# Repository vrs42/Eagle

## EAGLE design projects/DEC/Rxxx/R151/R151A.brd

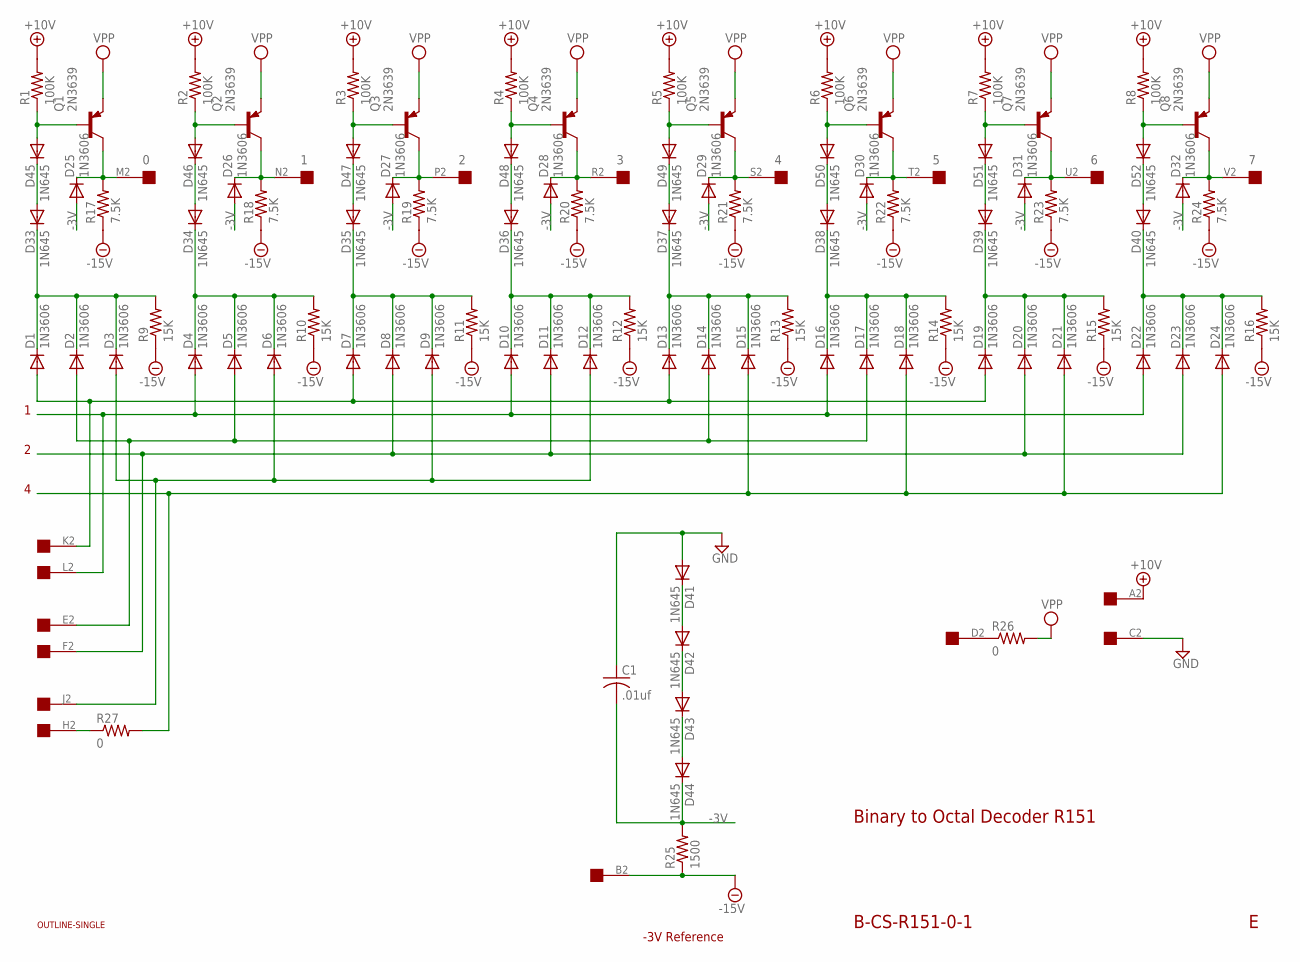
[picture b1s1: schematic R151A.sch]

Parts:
C1: .01uf; C050-025X075
D1, D2, D3, D4, D5, D6, D7, D8, D9, D10, D11, D12, D13, D14, D15, D16, D17, D18, D19, D20, D21, D22, D23, D24, D25, D26, D27, D28, D29, D30, D31, D32: 1N3606; DO35-10
D33, D34, D35, D36, D37, D38, D39, D40, D41, D42, D43, D44, D45, D46, D47, D48, D49, D50, D51, D52: 1N645; DO35-10
Q1, Q2, Q3, Q4, Q5, Q6, Q7, Q8: 2N3639; TO39
R1, R2, R3, R4, R5, R6, R7, R8: 100K; 0207/10
R9, R10, R11, R12, R13, R14, R15, R16: 15K; 0207/10
R17, R18, R19, R20, R21, R22, R23, R24: 7.5K; 0207/10
R25: 1500; 0207/10
R26, R27: 0; 0207/10
U$1: OUTLINE-SINGLE; SINGLE
U$2: EDGE-1; EDGE-CON1

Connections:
0: D25.C, Q1.3 (C), R17.2, U$2.M2
1: D26.C, Q2.3 (C), R18.2, U$2.N2
2: D27.C, Q3.3 (C), R19.2, U$2.P2
3: D28.C, Q4.3 (C), R20.2, U$2.R2
4: D29.C, Q5.3 (C), R21.2, U$2.S2
5: D30.C, Q6.3 (C), R22.2, U$2.T2
6: D31.C, Q7.3 (C), R23.2, U$2.U2
7: D32.C, Q8.3 (C), R24.2, U$2.V2
!D0: D1.A, D7.A, D13.A, D19.A, U$2.K2
!D1: D2.A, D5.A, D14.A, D17.A, U$2.E2
!D2: D3.A, D6.A, D9.A, D12.A, U$2.J2
+10V: R1.2, R2.2, R3.2, R4.2, R5.2, R6.2, R7.2, R8.2, U$2.A2
-3V: C1.2, D25.A, D26.A, D27.A, D28.A, D29.A, D30.A, D31.A, D32.A, D44.C, R25.2
-15V: R9.1, R10.1, R11.1, R12.1, R13.1, R14.1, R15.1, R16.1, R17.1, R18.1, R19.1, R20.1, R21.1, R22.1, R23.1, R24.1, R25.1, U$2.B2
D0: D4.A, D10.A, D16.A, D22.A, U$2.L2
D1: D8.A, D11.A, D20.A, D23.A, U$2.F2
D2: D15.A, D18.A, D21.A, D24.A, R27.2
GND: C1.1, D41.A, U$2.C2
unnamed: D46.A, Q2.2 (B), R2.1
unnamed: D41.C, D42.A
unnamed: R26.1, U$2.D2
unnamed: R27.1, U$2.H2
unnamed: D4.C, D5.C, D6.C, D34.C, R10.2
unnamed: D34.A, D46.C
unnamed: D47.A, Q3.2 (B), R3.1
unnamed: D7.C, D8.C, D9.C, D35.C, R11.2
unnamed: D35.A, D47.C
unnamed: D42.C, D43.A
unnamed: D43.C, D44.A
unnamed: D48.A, Q4.2 (B), R4.1
unnamed: D45.A, Q1.2 (B), R1.1
unnamed: D1.C, D2.C, D3.C, D33.C, R9.2
unnamed: D33.A, D45.C
unnamed: D10.C, D11.C, D12.C, D36.C, R12.2
unnamed: D36.A, D48.C
unnamed: D49.A, Q5.2 (B), R5.1
unnamed: D13.C, D14.C, D15.C, D37.C, R13.2
unnamed: D37.A, D49.C
unnamed: D50.A, Q6.2 (B), R6.1
unnamed: D16.C, D17.C, D18.C, D38.C, R14.2
unnamed: D38.A, D50.C
unnamed: D51.A, Q7.2 (B), R7.1
unnamed: D19.C, D20.C, D21.C, D39.C, R15.2
unnamed: D39.A, D51.C
unnamed: D52.A, Q8.2 (B), R8.1
unnamed: D22.C, D23.C, D24.C, D40.C, R16.2
unnamed: D40.A, D52.C
VPP: Q1.1 (E), Q2.1 (E), Q3.1 (E), Q4.1 (E), Q5.1 (E), Q6.1 (E), Q7.1 (E), Q8.1 (E), R26.2

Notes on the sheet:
Binary to Octal Decoder R151
B-CS-R151-0-1
-3V Reference

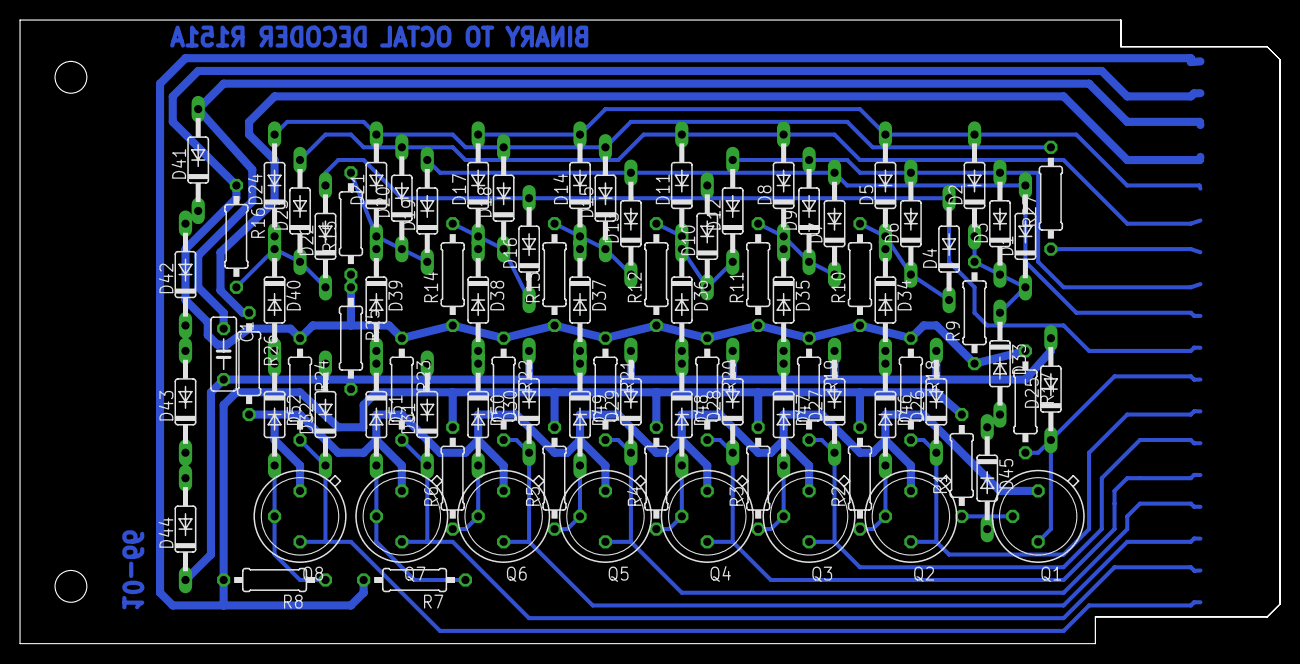
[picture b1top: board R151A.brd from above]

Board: 2 copper layers, 125.7 x 62.2 mm, 90 parts (0 on the bottom side), 48 nets.

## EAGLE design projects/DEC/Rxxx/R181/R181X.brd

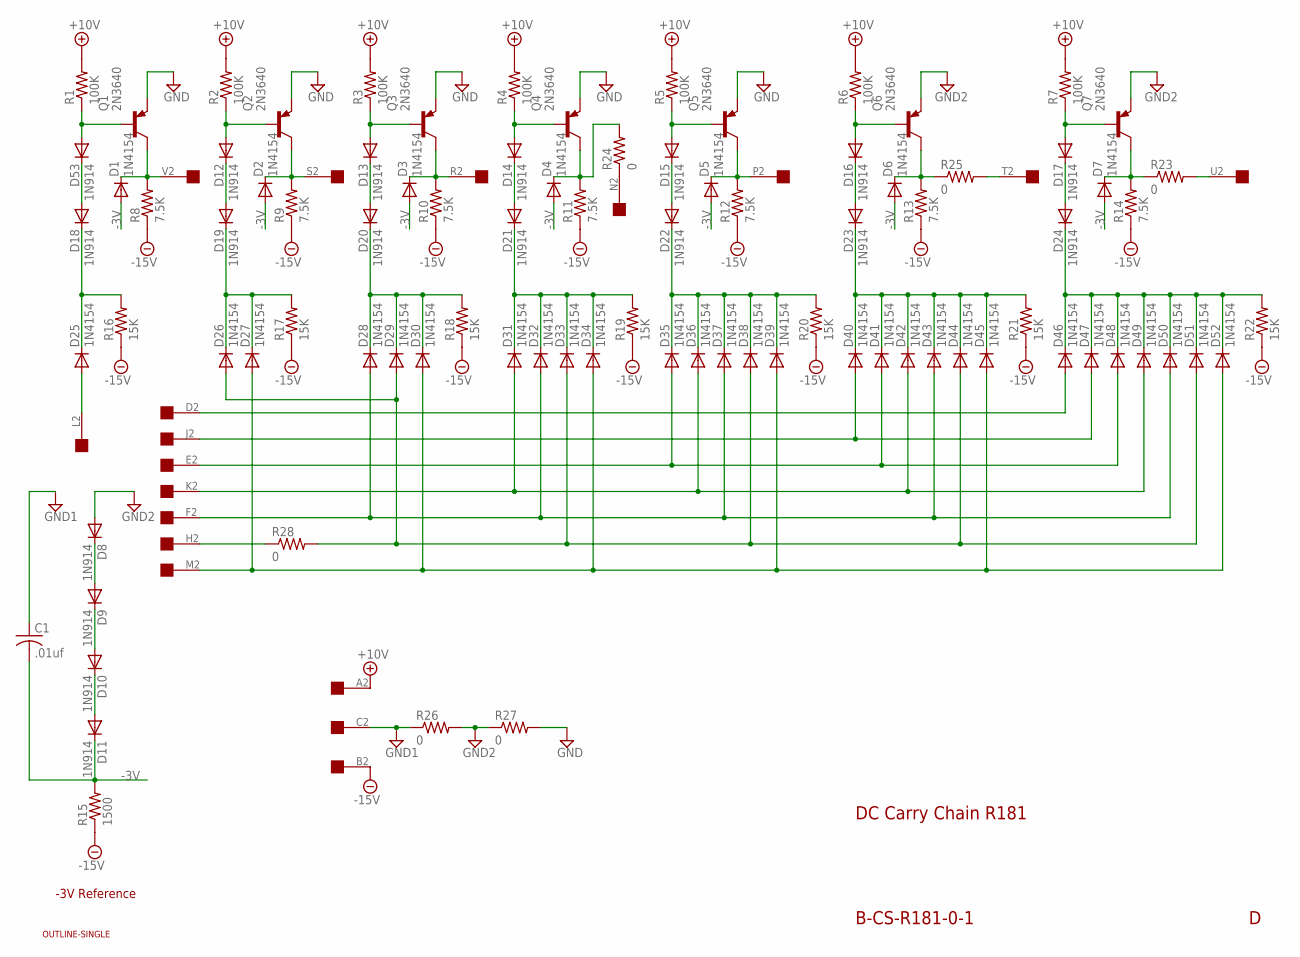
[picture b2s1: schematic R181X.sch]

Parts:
C1: .01uf; C050-025X075
D1, D2, D3, D4, D5, D6, D7, D25, D26, D27, D28, D29, D30, D31, D32, D33, D34, D35, D36, D37, D38, D39, D40, D41, D42, D43, D44, D45, D46, D47, D48, D49, D50, D51, D52: 1N4154; DO35-10
D8, D9, D10, D11, D12, D13, D14, D15, D16, D17, D18, D19, D20, D21, D22, D23, D24, D53: 1N914; DO35-10
Q1, Q2, Q3, Q4, Q5, Q6, Q7: 2N3640; TO39
R1, R2, R3, R4, R5, R6, R7: 100K; 0207/10
R8, R9, R10, R11, R12, R13, R14: 7.5K; 0207/10
R15: 1500; 0207/10
R16, R17, R18, R19, R20, R21, R22: 15K; 0207/10
R23, R24, R25, R26, R27, R28: 0; 0207/10
U$1: OUTLINE-SINGLE; SINGLE
U$2: EDGE-1; EDGE-CON1

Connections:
+10V: R1.2, R2.2, R3.2, R4.2, R5.2, R6.2, R7.2, U$2.A2
-3V: C1.2, D1.A, D2.A, D3.A, D4.A, D5.A, D6.A, D7.A, D11.C, R15.2
-15V: R8.1, R9.1, R10.1, R11.1, R12.1, R13.1, R14.1, R15.1, R16.1, R17.1, R18.1, R19.1, R20.1, R21.1, R22.1, U$2.B2
GND: Q1.1 (E), Q2.1 (E), Q3.1 (E), Q4.1 (E), Q5.1 (E), R27.2
GND1: C1.1, R26.1, U$2.C2
GND2: D8.A, Q6.1 (E), Q7.1 (E), R26.2, R27.1
N: D4.C, Q4.3 (C), R11.2, R24.2
unnamed: D26.A, D29.A, D33.A, D38.A, D44.A, D51.A, R28.2
unnamed: D12.A, Q2.2 (B), R2.1
unnamed: D8.C, D9.A
unnamed: R28.1, U$2.H2
unnamed: D25.A, U$2.L2
unnamed: D19.C, D26.C, D27.C, R17.2
unnamed: D12.C, D19.A
unnamed: D13.A, Q3.2 (B), R3.1
unnamed: D27.A, D30.A, D34.A, D39.A, D45.A, D52.A, U$2.M2
unnamed: D35.A, D41.A, D48.A, U$2.E2
unnamed: D20.C, D28.C, D29.C, D30.C, R18.2
unnamed: D13.C, D20.A
unnamed: D9.C, D10.A
unnamed: D28.A, D32.A, D37.A, D43.A, D50.A, U$2.F2
unnamed: D31.A, D36.A, D42.A, D49.A, U$2.K2
unnamed: D10.C, D11.A
unnamed: R23.2, U$2.U2
unnamed: D14.A, Q4.2 (B), R4.1
unnamed: D53.A, Q1.2 (B), R1.1
unnamed: D40.A, D47.A, U$2.J2
unnamed: R25.2, U$2.T2
unnamed: D18.C, D25.C, R16.2
unnamed: D18.A, D53.C
unnamed: D46.A, U$2.D2
unnamed: R24.1, U$2.N2
unnamed: D21.C, D31.C, D32.C, D33.C, D34.C, R19.2
unnamed: D14.C, D21.A
unnamed: D15.A, Q5.2 (B), R5.1
unnamed: D22.C, D35.C, D36.C, D37.C, D38.C, D39.C, R20.2
unnamed: D15.C, D22.A
unnamed: D16.A, Q6.2 (B), R6.1
unnamed: D23.C, D40.C, D41.C, D42.C, D43.C, D44.C, D45.C, R21.2
unnamed: D16.C, D23.A
unnamed: D17.A, Q7.2 (B), R7.1
unnamed: D24.C, D46.C, D47.C, D48.C, D49.C, D50.C, D51.C, D52.C, R22.2
unnamed: D17.C, D24.A
P: D5.C, Q5.3 (C), R12.2, U$2.P2
R: D3.C, Q3.3 (C), R10.2, U$2.R2
S: D2.C, Q2.3 (C), R9.2, U$2.S2
T: D6.C, Q6.3 (C), R13.2, R25.1
U: D7.C, Q7.3 (C), R14.2, R23.1
V: D1.C, Q1.3 (C), R8.2, U$2.V2

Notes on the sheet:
DC Carry Chain R181
B-CS-R181-0-1
-3V Reference

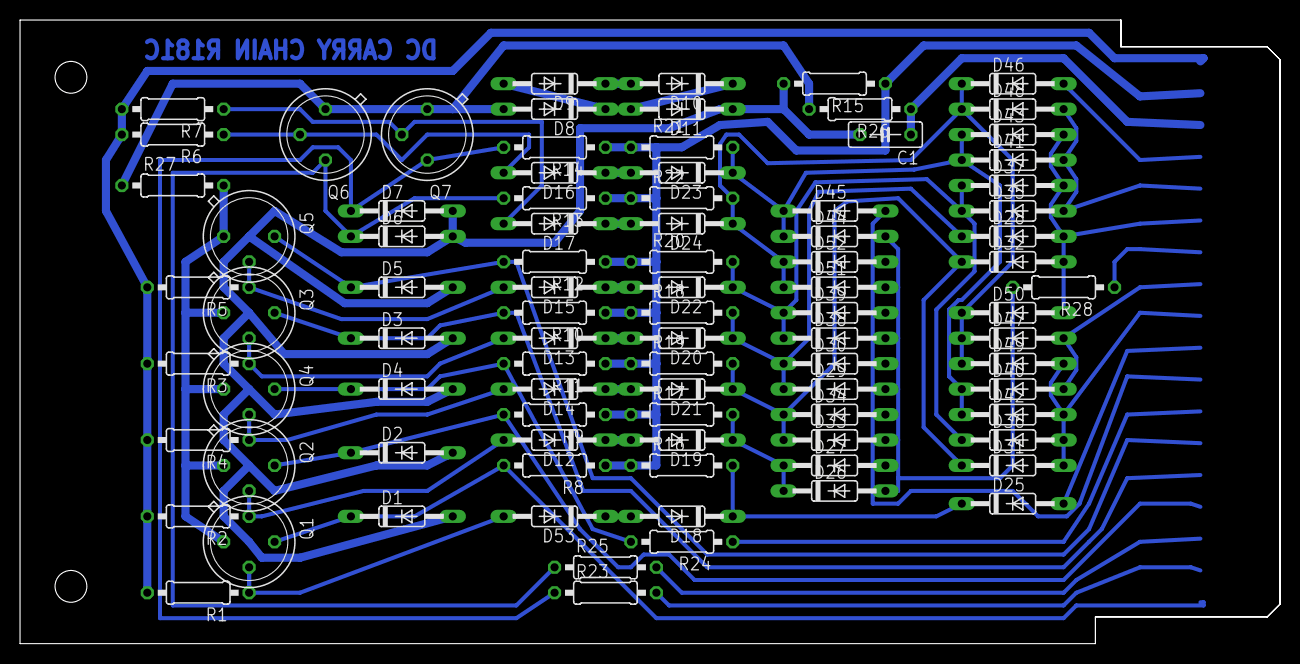
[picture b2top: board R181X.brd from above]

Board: 2 copper layers, 125.7 x 62.2 mm, 91 parts (0 on the bottom side), 49 nets.

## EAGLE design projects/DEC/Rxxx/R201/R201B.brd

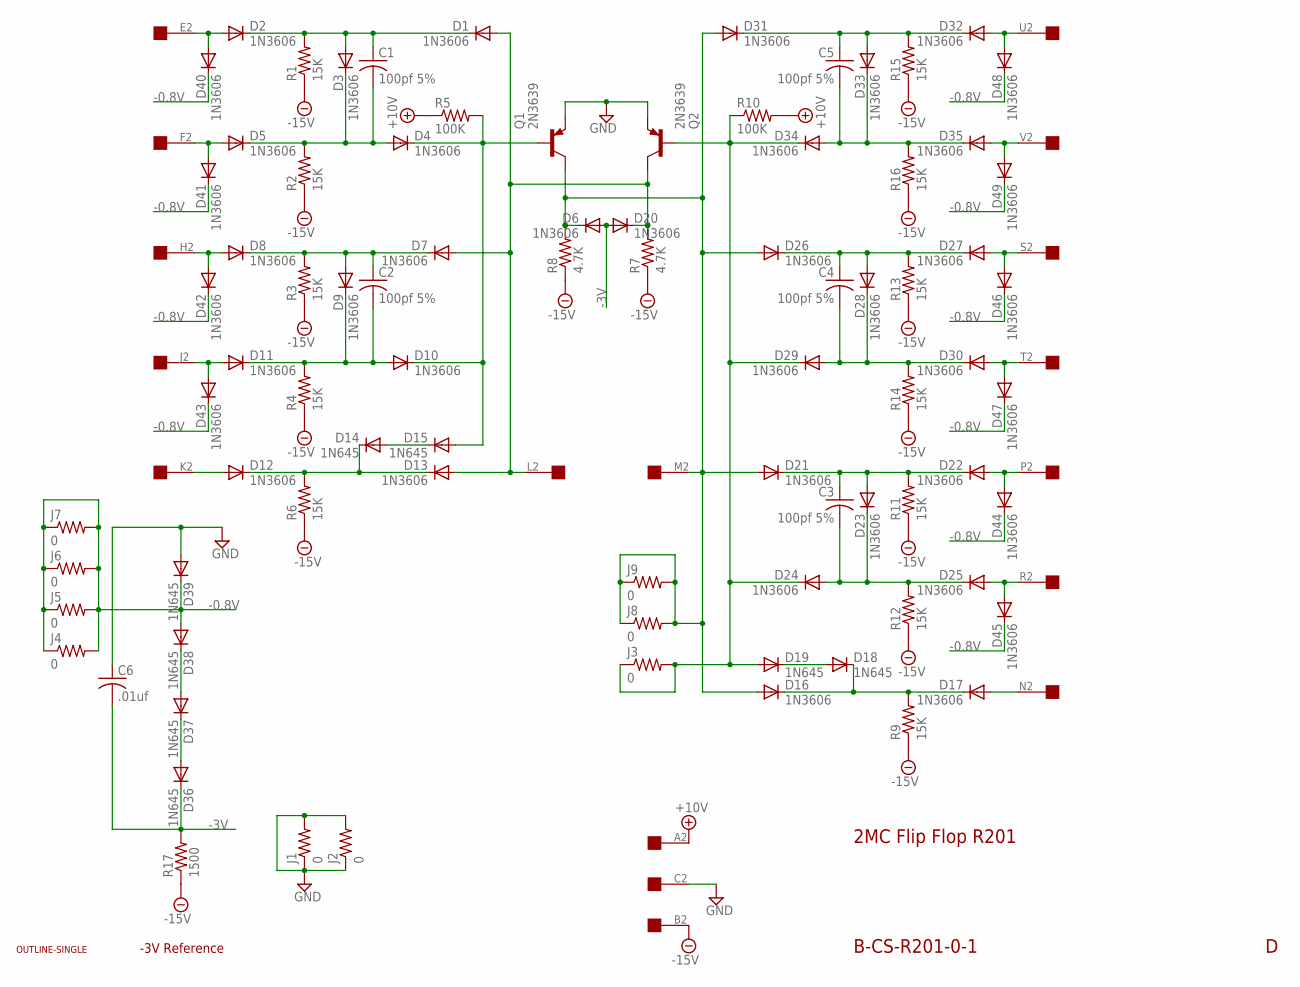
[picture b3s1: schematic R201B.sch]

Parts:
C1, C2, C3, C4, C5: 100pf 5%; C063-025X075
C6: .01uf; C063-025X075
D1, D2, D3, D4, D5, D6, D7, D8, D9, D10, D11, D12, D13, D16, D17, D20, D21, D22, D23, D24, D25, D26, D27, D28, D29, D30, D31, D32, D33, D34, D35, D40, D41, D42, D43, D44, D45, D46, D47, D48, D49: 1N3606; DO35-10
D14, D15, D18, D19, D36, D37, D38, D39: 1N645; DO35-10
J1, J2, J3, J4, J5, J6, J7, J8, J9: 0; 0207/10
Q1, Q2: 2N3639; TO39
R1, R2, R3, R4, R6, R9, R11, R12, R13, R14, R15, R16: 15K; 0207/10
R5, R10: 100K; 0207/10
R7, R8: 4.7K; 0207/10
R17: 1500; 0207/10
U$1: OUTLINE-SINGLE; SINGLE
U$2: EDGE-1; EDGE-CON1

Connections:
+10V: R5.1, R10.2, U$2.A2
-0.8V: D38.A, D39.C, D40.C, D41.C, D42.C, D43.C, D44.C, D45.C, D46.C, D47.C, D48.C, D49.C, J4.1, J4.2, J5.1, J5.2, J6.1, J6.2, J7.1, J7.2
-3V: C6.2, D6.A, D20.A, D36.C, R17.2
-15V: R1.1, R2.1, R3.1, R4.1, R6.1, R7.1, R8.1, R9.1, R11.1, R12.1, R13.1, R14.1, R15.1, R16.1, R17.1, U$2.B2
GND: C6.1, D39.A, J1.1, J1.2, J2.1, J2.2, Q1.1 (E), Q2.1 (E), U$2.C2
L: D1.A, D7.A, D13.A, D20.C, Q2.3 (C), R7.2, U$2.L2
M: D6.C, D16.A, D21.A, D26.A, D31.A, J8.1, J8.2, J9.1, J9.2, Q1.3 (C), R8.2, U$2.M2
unnamed: D5.A, D41.A, U$2.F2
unnamed: C5.1, D31.C, D32.C, D33.A, R15.2
unnamed: C1.2, D3.C, D4.A, D5.C, R2.2
unnamed: C1.1, D1.C, D2.C, D3.A, R1.2
unnamed: D12.A, U$2.K2
unnamed: D19.A, D24.C, D29.C, D34.C, J3.1, J3.2, Q2.2 (B), R10.1
unnamed: D32.A, D48.A, U$2.U2
unnamed: C5.2, D33.C, D34.A, D35.C, R16.2
unnamed: D17.A, U$2.N2
unnamed: D2.A, D40.A, U$2.E2
unnamed: D35.A, D49.A, U$2.V2
unnamed: D18.A, D19.C
unnamed: D37.A, D38.C
unnamed: D4.C, D10.C, D15.A, Q1.2 (B), R5.2
unnamed: D14.A, D15.C
unnamed: D36.A, D37.C
unnamed: D22.A, D44.A, U$2.P2
unnamed: D12.C, D13.C, D14.C, R6.2
unnamed: D8.A, D42.A, U$2.H2
unnamed: D16.C, D17.C, D18.C, R9.2
unnamed: D11.A, D43.A, U$2.J2
unnamed: C2.2, D9.C, D10.A, D11.C, R4.2
unnamed: D27.A, D46.A, U$2.S2
unnamed: C2.1, D7.C, D8.C, D9.A, R3.2
unnamed: D30.A, D47.A, U$2.T2
unnamed: C4.2, D28.C, D29.A, D30.C, R14.2
unnamed: C4.1, D26.C, D27.C, D28.A, R13.2
unnamed: D25.A, D45.A, U$2.R2
unnamed: C3.2, D23.C, D24.A, D25.C, R12.2
unnamed: C3.1, D21.C, D22.C, D23.A, R11.2

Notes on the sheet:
2MC Flip Flop R201
B-CS-R201-0-1
-3V Reference

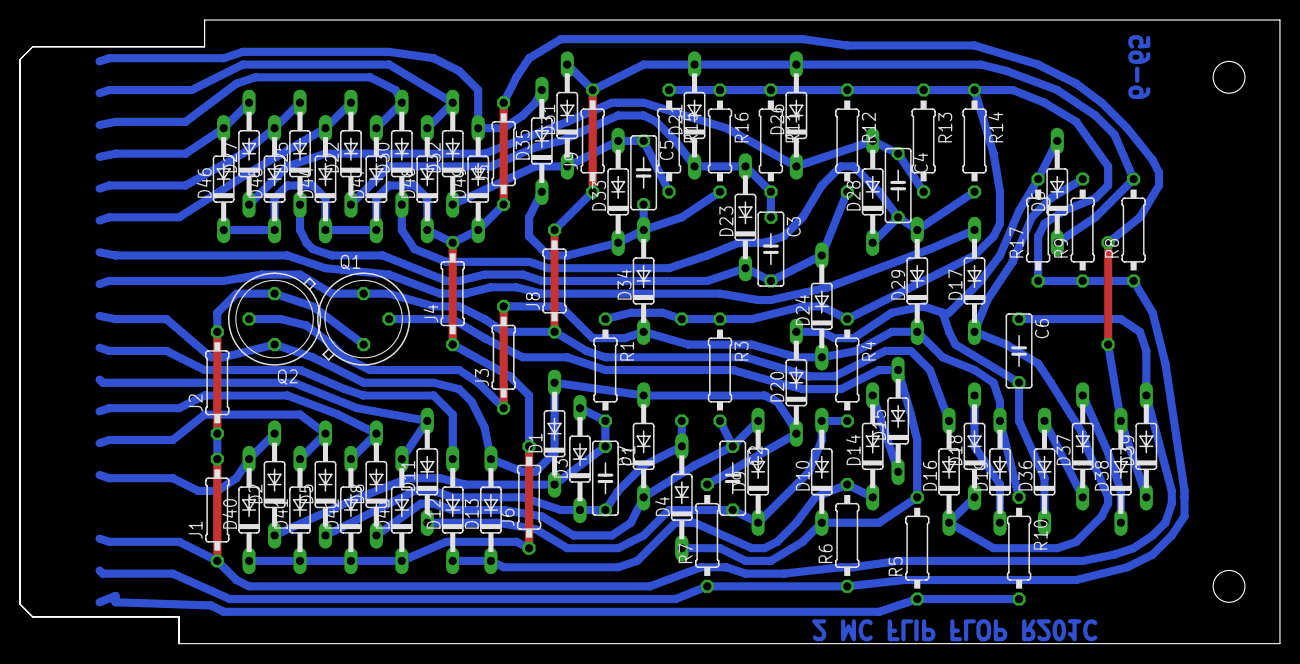
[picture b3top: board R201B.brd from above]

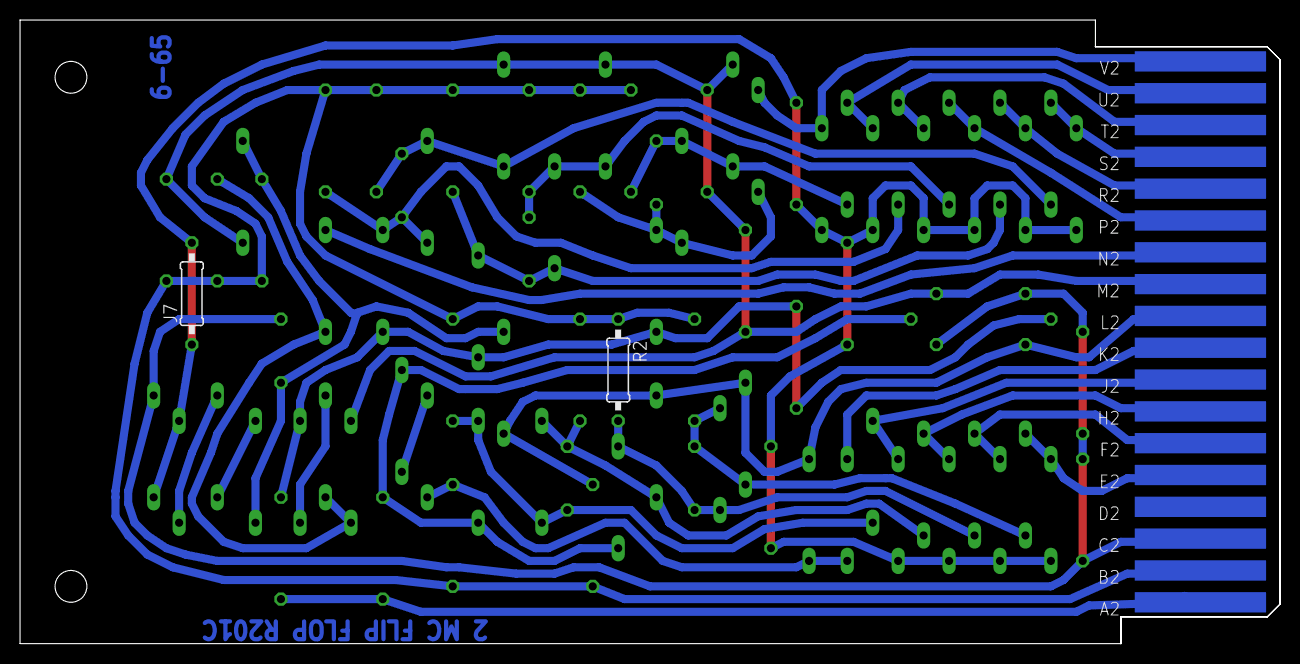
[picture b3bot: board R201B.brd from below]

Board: 2 copper layers, 125.7 x 62.2 mm, 85 parts (2 on the bottom side), 37 nets.
